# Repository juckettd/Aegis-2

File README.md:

# Aegis-2
The Aegis 2 Handheld with a 7" screen

NOTE: This is still a work in progress.

## Summary

The Aegis 2 is a DIY handheld that uses a 3D printed case with a Raspberry Pi CM4 and 1920x1200 7" screen.

## Building the Handheld

To build the handheld you will need the items listed as required in the Bill of Materials along with the following tools:

Reflow Station or Reflow Oven<br/>
Solding Iron<br/>
Solder Paste<br/>
Tweezers<br/>
Small Philips Screw Driver<br/>
Small Flathead Screw Driver<br/>
Super Glue (preferrably CA glue with Accelerator)

There are items in the Bill of Materials that are listed as optional. These items are not required to get a working device but can be used if desired. At this time I will not provide directions on how to use the optional components so use at your discretion.

### Assembling the Circuit Board

The custom circuit boards are provided as fusion 360 files in this repository. This includes the schematic, board layout, and the gerber files. 

To get the boards printed, a manufacturing facility is required. The website jlcpcb.com was used to print the 3 circuit board prototypes for the design. The larger of the two boards uses 4 layers, and the smaller ones use only 2 layers. It is recommended to also get the stencils with the boards so that applying the solder paste becomes much easier.

Once the boards have been received you will need to assemble the circuitry on the boards. This is done by getting all of the components provided in the bill of materials. Each item has a provided Link to where the item can be acquired along with the price at the time of the assembly of the prototype. After acquiring all of the components, use the stencil to apply solder paste to the circuit boards and then use tweezers to place each component. A reflow oven or reflow station should then be used to melt the solder paste and adhere the components. Lastly, any through hole components were then added on the using a soldering iron. 

Note: The teensy that is soldered to the board using the through holes. However, there are 4 pads that are located near the USB connector of the Teensy on the custom circuit board. They are the VBUS, D+, D-, and GND connections. I included the VBUS and GND connections as backups but they are not needed as the power and ground comes from the pins. But the D+, D- connections need to be connected to the teensy. On the underside of the teensy there are 4 pads that are in about the same location, a wire or some other form of connection is needed to connect the D+ from the teensy to the D+ on the custom circuit board, do the same with the D- connection.

While anyone who has experience with circuit boards will have their own method for assembling these boards I used the following steps and it is what I recommend for anyone without experience and a reflow oven (but a reflow station is required):
1. Using the stencil, put solder paste on the larger of the two boards on the side with a majority of the components
2. Place all of the surface mount components on that side of the board
3. Use a reflow station and heat the underside of the board until the solder paste on the top side melts to adhere the components. A tool to prop up the PCB comes in handy here. In my opinion this part is essential as some of the components are plastic and the hot air coming out of a reflow station can melt them.
4. Use a soldering iron to clean up an connections that didn't connect completely (You can watch youtube videos on how to do this, just search for solding iron and surface mount components)
5. Flip the board over and redo steps 1-4 for the underside of the board. Since these components are larger I just used the a soldering iron for all of the components, but the same procedure with the reflow station can be used. Just be careful with the hot air hitting components you have already put down, as they can fall off if the solder paste melts again.
6. Perform 1-5 for the second board and the few surface mount components that are on that board
7. Add all of the through hole items to both boards with a soldering iron (again youtube is your friend)

### Install Teensy Code

Before (or after) the circuit board has been assembled the teensy code needs to be pushed to the teensy. The teensy code is provided in the repo and you will need to follow the instructions on the teensy website for pushing code. Make sure that you set the board type to "XInput" otherwise it won't be seen as a XBox 360 Controller.

### 3D Printed Case

The files provided here for the case. They are printed in sections so that a printer with a standard bed size of 220mm x 220mm can be used print the case. Once they are printed they will have to be cleaned up and then glued together. Depending on which angle you choose to print the parts the cleanup step could be more or less cumbersome for the remove of support and getting good glue joints. I choose to print everything with flat surfaces on the bed to keep the post processing steps as easy as possible.

Once everything is glued together then no post processing on the outside is technically required to assemble the device. However, I chose to use filler, sand paper, and paint to get a really clean looking finish. The level of detail you desire on your handheld will be up to you based on how much effort you want to devote. Refer to youtube for how to sand and paint a 3D printed piece. However, try to keep the inside of the device as paint free as possible as the internal structure is already at the correct dimensions for the internal components.

I would also sand down the holes where the buttons will be located as they will to be rough from the 3D printing process. This can cause the buttons to stick. I would also check the shoulder buttons to make sure there is not any friction preventing them from moving properly. If there is then sand down the appropriate areas.

### Assembly

Once the case and the PCB have been built and are ready to go the handheld can be assembled.

TODO: Assembly Instructions

## Software

The Raspberry PI OS Buster version or Retropie both work. To get Bullseye working we need a new video driver that is not available yet. I've made a temporary one and will provide it here when I test it out.

The Config files provided that setup the device will install a monitor program that looks for the button presses for the power/reset/volume/misc. And like the previous handheld I built it will also eventually provide an overlay that will show battery/wifi status along with volume/brightness. However, the overlay does not work yet so that part of the code is commented out. But the monitor script does work for the buttons.

### /boot/config.txt

Regardless of which CM4 you use and which method is used to load the OS, you will need to add the following lines to the /boot/config.txt file. These are also listed in the /Config/boot/config.txt file in this repository:

dtoverlay=dwc2,dr_mode=host<br/>
h264_freq=333

The lines above will optimize the graphics for Moonlight (if you choose to use it to stream PC games) and will enable USB 2.0 on the device to get the Teensy and external USB ports working.

### First Boot

TODO

### System Setup

TODO

## Pictures/Videos

The are Videos of it working and Images are included in the Images folder:

Zelda: https://www.youtube.com/watch?v=uxBjKsduhgc

Super Mario World: https://www.youtube.com/watch?v=D417fbmwBnU

## Credits

Safe shutdown script
https://github.com/crcerror/ES-generic-shutdown/blob/master/multi_switch.sh

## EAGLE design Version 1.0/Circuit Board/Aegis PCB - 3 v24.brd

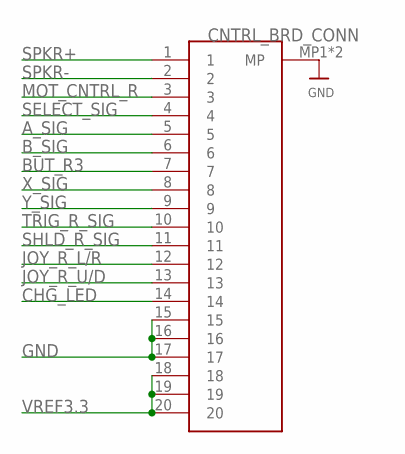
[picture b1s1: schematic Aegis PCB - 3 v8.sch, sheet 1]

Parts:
CNTRL_BRD_CONN: CONN-0527462033

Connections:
A_SIG: CNTRL_BRD_CONN.5; also elsewhere on the board
BUT_R3: CNTRL_BRD_CONN.7; also elsewhere on the board
B_SIG: CNTRL_BRD_CONN.6; also elsewhere on the board
CHG_LED: CNTRL_BRD_CONN.14; also elsewhere on the board
GND: CNTRL_BRD_CONN.15, CNTRL_BRD_CONN.16, CNTRL_BRD_CONN.17, CNTRL_BRD_CONN.MP1 (MP), CNTRL_BRD_CONN.MP2 (MP); also elsewhere on the board
JOY_R_L/R: CNTRL_BRD_CONN.12; also elsewhere on the board
JOY_R_U/D: CNTRL_BRD_CONN.13; also elsewhere on the board
MOT_CNTRL_R: CNTRL_BRD_CONN.3; also elsewhere on the board
SELECT_SIG: CNTRL_BRD_CONN.4; also elsewhere on the board
SHLD_R_SIG: CNTRL_BRD_CONN.11; also elsewhere on the board
SPKR+: CNTRL_BRD_CONN.1; also elsewhere on the board
SPKR-: CNTRL_BRD_CONN.2; also elsewhere on the board
TRIG_R_SIG: CNTRL_BRD_CONN.10; also elsewhere on the board
VREF3.3: CNTRL_BRD_CONN.18, CNTRL_BRD_CONN.19, CNTRL_BRD_CONN.20; also elsewhere on the board
X_SIG: CNTRL_BRD_CONN.8; also elsewhere on the board
Y_SIG: CNTRL_BRD_CONN.9; also elsewhere on the board

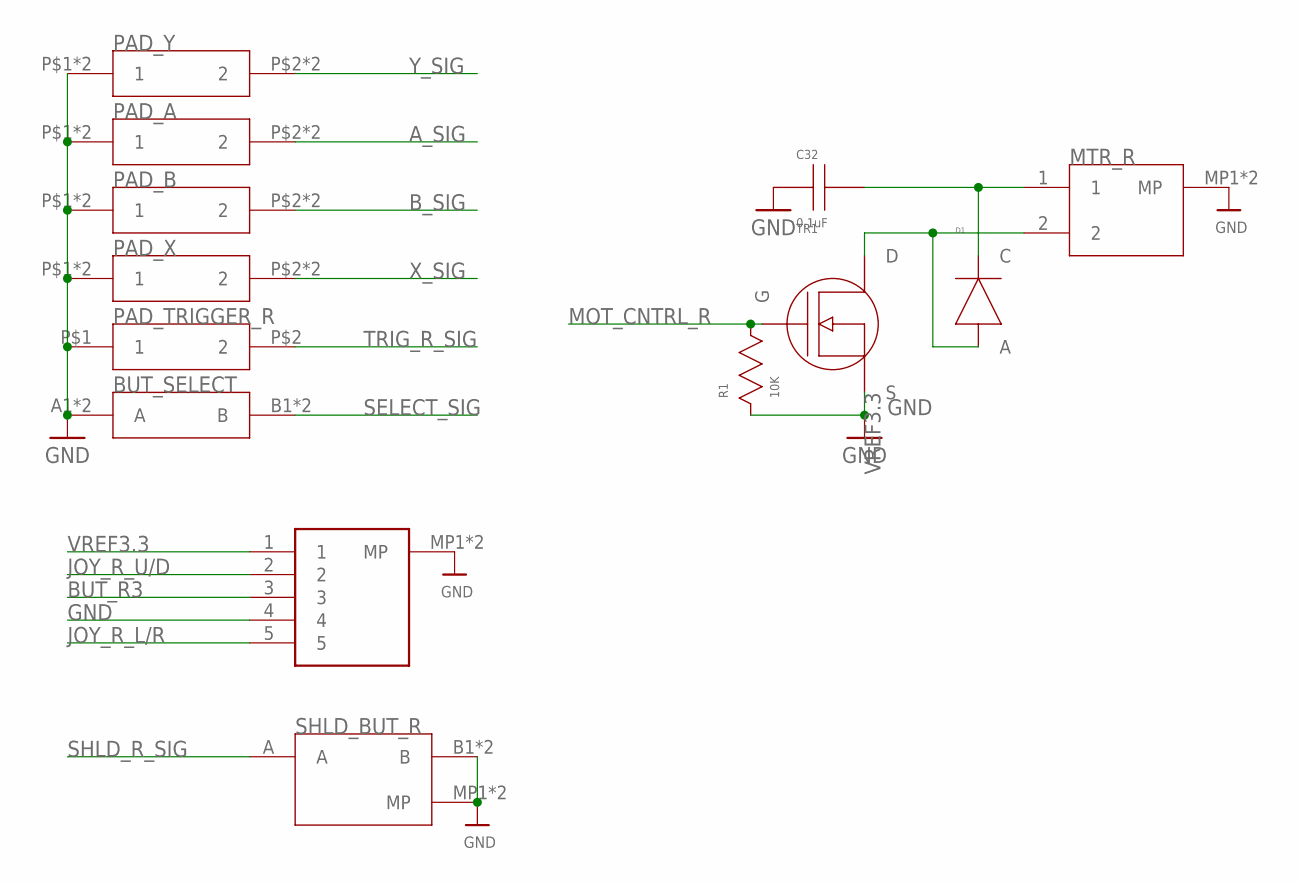
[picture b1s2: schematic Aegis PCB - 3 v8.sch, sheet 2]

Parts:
BUT_SELECT: BUT-R-667834
C32: 0.1uF; CAP-603
D1: DIODE-X3-WLB1608-2
JOYSTICK_R: CONN-046809605110846+
MTR_R: CONN-0781710002
PAD_A: AEGIS-BUTTONPAD
PAD_B: AEGIS-BUTTONPAD
PAD_TRIGGER_R: AEGIN-SHLDPAD
PAD_X: AEGIS-BUTTONPAD
PAD_Y: AEGIS-BUTTONPAD
R1: 10K; RES-603
SHLD_BUT_R: AEGIN-SHLDBUT
TR1: TRAN-DMG2302UKQ

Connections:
A_SIG: PAD_A.P$2 (2), PAD_A.P$4 (2); also elsewhere on the board
BUT_R3: JOYSTICK_R.3; also elsewhere on the board
B_SIG: PAD_B.P$2 (2), PAD_B.P$4 (2); also elsewhere on the board
GND: BUT_SELECT.A1 (A), BUT_SELECT.A2 (A), C32.A, JOYSTICK_R.4, JOYSTICK_R.MP1 (MP), JOYSTICK_R.MP2 (MP), MTR_R.MP1 (MP), MTR_R.MP2 (MP), PAD_A.P$1 (1), PAD_A.P$3 (1), PAD_B.P$1 (1), PAD_B.P$3 (1), PAD_TRIGGER_R.P$1 (1), PAD_X.P$1 (1), PAD_X.P$3 (1), PAD_Y.P$1 (1), PAD_Y.P$3 (1), R1.A, SHLD_BUT_R.B1 (B), SHLD_BUT_R.B2 (B), SHLD_BUT_R.MP1 (MP), SHLD_BUT_R.MP2 (MP), TR1.S; also elsewhere on the board
JOY_R_L/R: JOYSTICK_R.5; also elsewhere on the board
JOY_R_U/D: JOYSTICK_R.2; also elsewhere on the board
MOT_CNTRL_R: R1.C, TR1.G; also elsewhere on the board
unnamed: D1.A, MTR_R.2, TR1.D
SELECT_SIG: BUT_SELECT.B1 (B), BUT_SELECT.B2 (B); also elsewhere on the board
SHLD_R_SIG: SHLD_BUT_R.A; also elsewhere on the board
TRIG_R_SIG: PAD_TRIGGER_R.P$2 (2); also elsewhere on the board
VREF3.3: C32.C, D1.C, JOYSTICK_R.1, MTR_R.1; also elsewhere on the board
X_SIG: PAD_X.P$2 (2), PAD_X.P$4 (2); also elsewhere on the board
Y_SIG: PAD_Y.P$2 (2), PAD_Y.P$4 (2); also elsewhere on the board

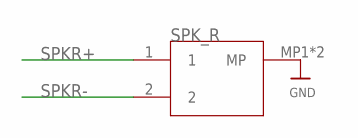
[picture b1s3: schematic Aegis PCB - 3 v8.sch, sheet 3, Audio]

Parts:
SPK_R: CONN-0781710002

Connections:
GND: SPK_R.MP1 (MP), SPK_R.MP2 (MP); also elsewhere on the board
SPKR+: SPK_R.1; also elsewhere on the board
SPKR-: SPK_R.2; also elsewhere on the board

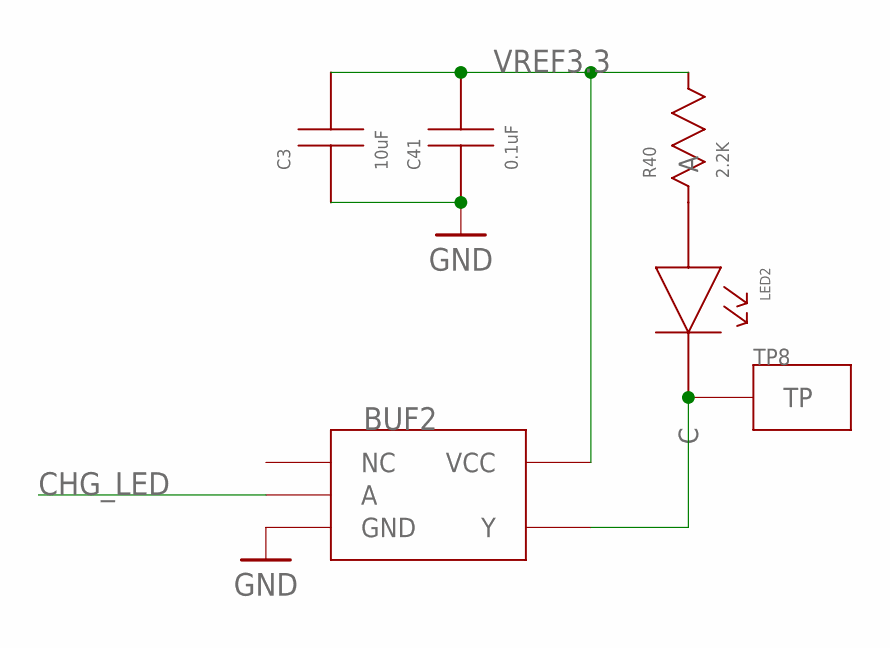
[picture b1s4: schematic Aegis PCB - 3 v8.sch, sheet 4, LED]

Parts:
BUF2: BUF-74LVC1G07
C3: 10uF; CAP-603
C41: 0.1uF; CAP-603
LED2: LED-SM0805UWC
R40: 2.2K; RES-603
TP8: TESTPOINT

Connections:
CHG_LED: BUF2.A; also elsewhere on the board
GND: BUF2.GND, C3.A, C41.A; also elsewhere on the board
unnamed: LED2.A, R40.A
unnamed: BUF2.Y, LED2.C, TP8.TP
VREF3.3: BUF2.VCC, C3.C, C41.C, R40.C; also elsewhere on the board

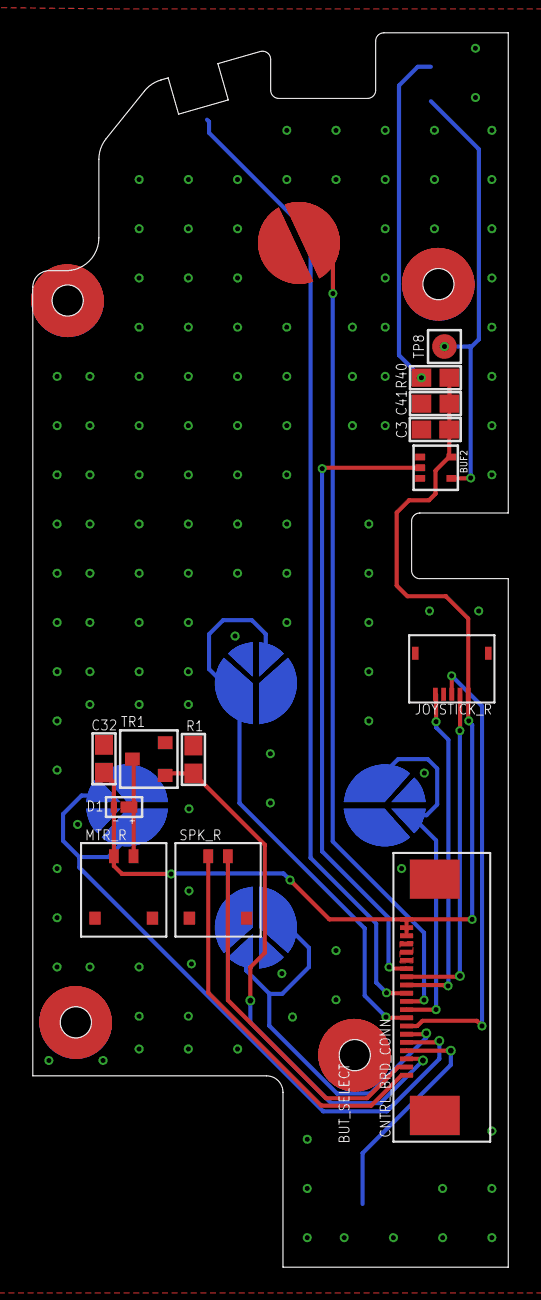
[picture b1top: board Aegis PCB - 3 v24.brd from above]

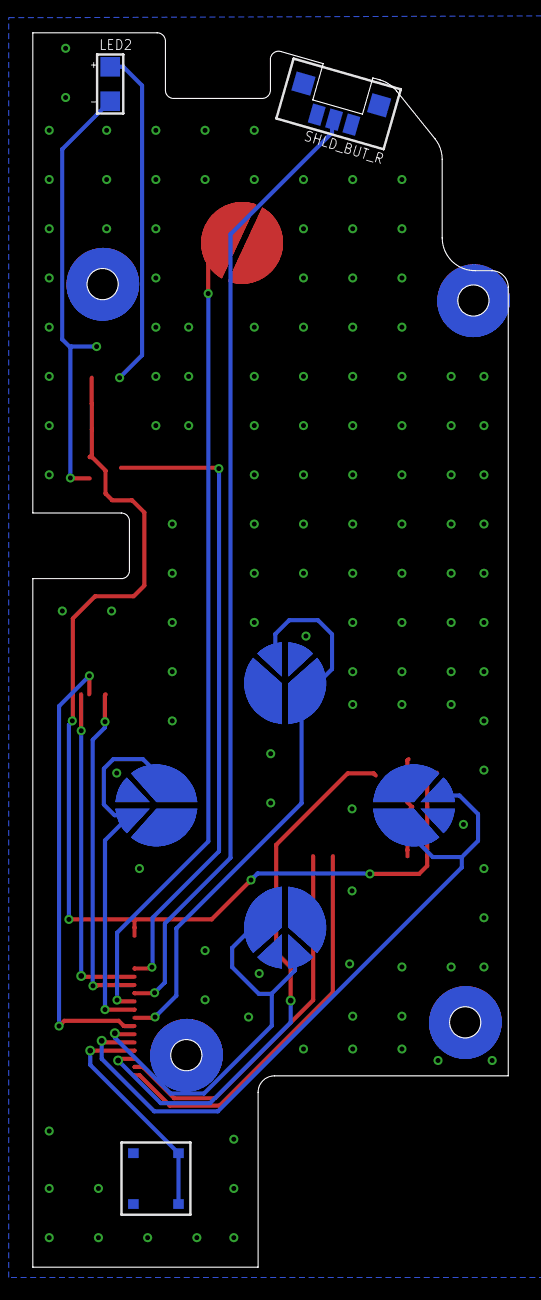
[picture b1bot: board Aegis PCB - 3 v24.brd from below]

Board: 2 copper layers, 29.0 x 75.2 mm, 21 parts (7 on the bottom side), 19 nets.

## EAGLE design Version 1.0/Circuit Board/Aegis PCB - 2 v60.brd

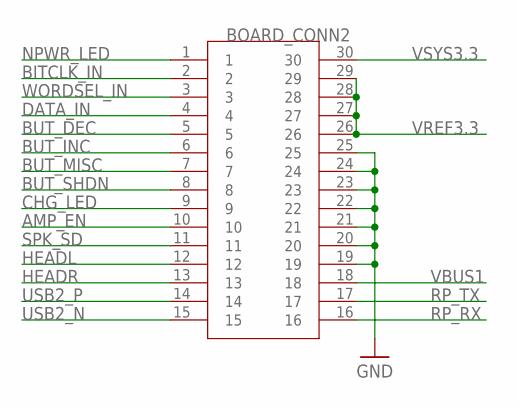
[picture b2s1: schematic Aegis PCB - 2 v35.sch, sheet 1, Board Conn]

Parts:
BOARD_CONN2: CONN-AXK6F30347YG

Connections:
AMP_EN: BOARD_CONN2.10; also elsewhere on the board
BITCLK_IN: BOARD_CONN2.2; also elsewhere on the board
BUT_DEC: BOARD_CONN2.5; also elsewhere on the board
BUT_INC: BOARD_CONN2.6; also elsewhere on the board
BUT_MISC: BOARD_CONN2.7; also elsewhere on the board
BUT_SHDN: BOARD_CONN2.8; also elsewhere on the board
CHG_LED: BOARD_CONN2.9; also elsewhere on the board
DATA_IN: BOARD_CONN2.4; also elsewhere on the board
GND: BOARD_CONN2.19, BOARD_CONN2.20, BOARD_CONN2.21, BOARD_CONN2.22, BOARD_CONN2.23, BOARD_CONN2.24, BOARD_CONN2.25; also elsewhere on the board
HEADL: BOARD_CONN2.12; also elsewhere on the board
HEADR: BOARD_CONN2.13; also elsewhere on the board
NPWR_LED: BOARD_CONN2.1; also elsewhere on the board
RP_RX: BOARD_CONN2.16; also elsewhere on the board
RP_TX: BOARD_CONN2.17; also elsewhere on the board
SPK_SD: BOARD_CONN2.11; also elsewhere on the board
USB2_N: BOARD_CONN2.15; also elsewhere on the board
USB2_P: BOARD_CONN2.14; also elsewhere on the board
VBUS1: BOARD_CONN2.18; also elsewhere on the board
VREF3.3: BOARD_CONN2.26, BOARD_CONN2.27, BOARD_CONN2.28, BOARD_CONN2.29; also elsewhere on the board
VSYS3.3: BOARD_CONN2.30; also elsewhere on the board
WORDSEL_IN: BOARD_CONN2.3; also elsewhere on the board

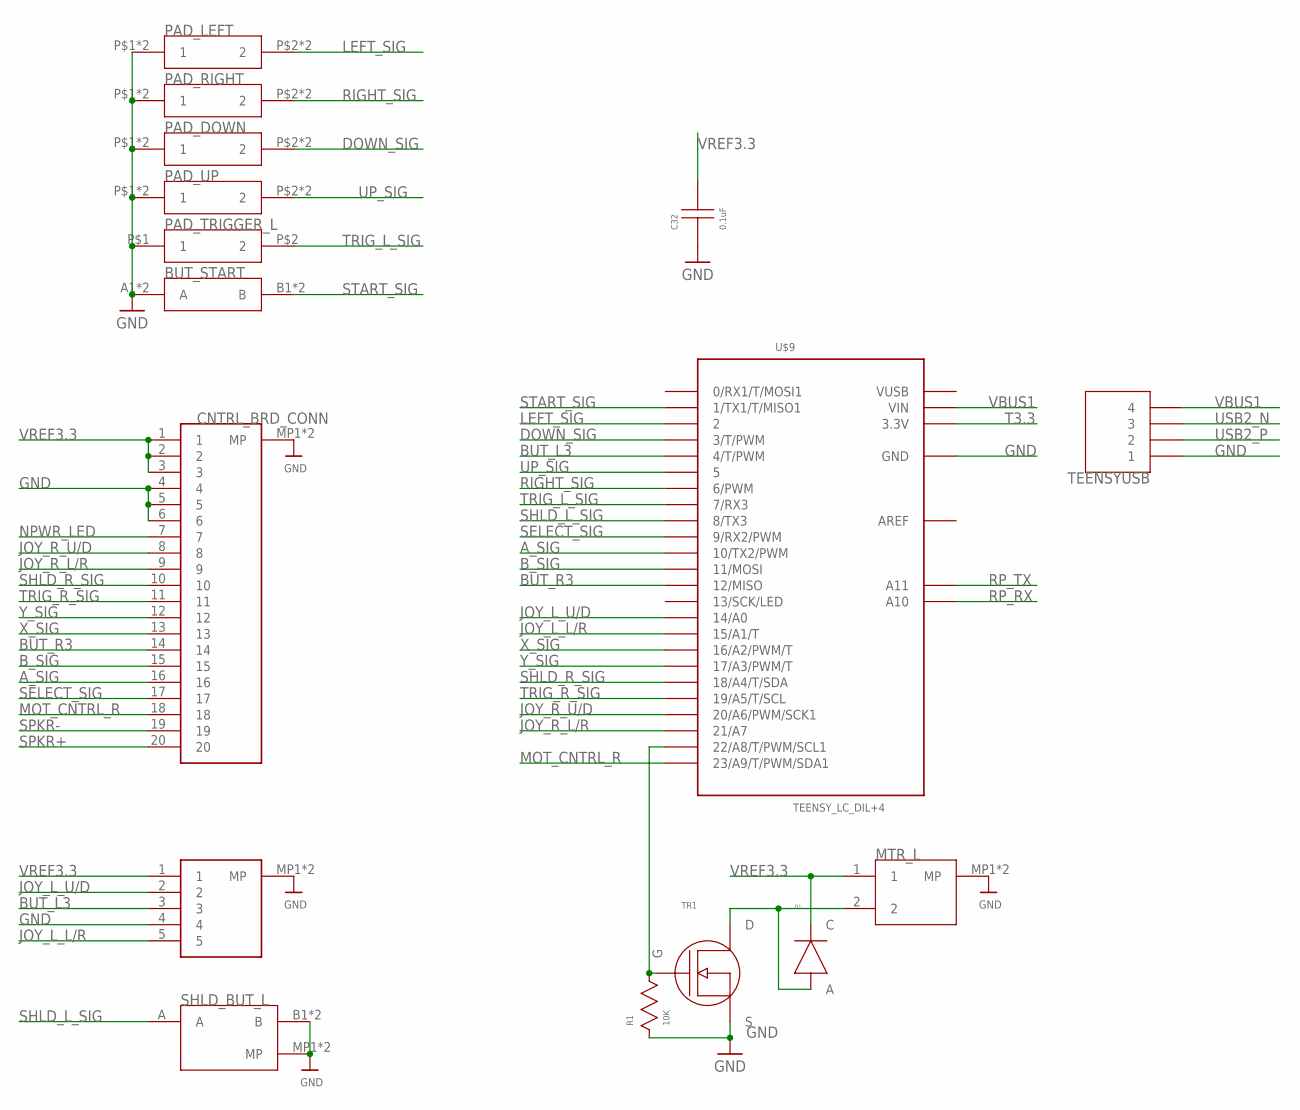
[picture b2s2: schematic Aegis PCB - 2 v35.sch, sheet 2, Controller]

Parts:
BUT_START: BUT-R-667834
C32: 0.1uF; CAP-603
CNTRL_BRD_CONN: CONN-0527462033
D1: DIODE-X3-WLB1608-2
JOYSTICK_L: CONN-046809605110846+
MTR_L: CONN-0781710002
PAD_DOWN: AEGIS-BUTTONPAD
PAD_LEFT: AEGIS-BUTTONPAD
PAD_RIGHT: AEGIS-BUTTONPAD
PAD_TRIGGER_L: AEGIN-SHLDPAD
PAD_UP: AEGIS-BUTTONPAD
R1: 10K; RES-603
SHLD_BUT_L: AEGIN-SHLDBUT
TEENSYUSB: CONN_4PIN
TR1: TRAN-DMG2302UKQ
U$9: TEENSY_LC_DIL+4; TEENSY_3.0-3.2&LC_DIL+4

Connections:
AREF: U$9.AREF
A_SIG: CNTRL_BRD_CONN.16, U$9.10 (10/TX2/PWM)
BUT_L3: JOYSTICK_L.3, U$9.4 (4/T/PWM)
BUT_R3: CNTRL_BRD_CONN.14, U$9.12 (12/MISO)
B_SIG: CNTRL_BRD_CONN.15, U$9.11 (11/MOSI)
DOWN_SIG: PAD_DOWN.P$2 (2), PAD_DOWN.P$4 (2), U$9.3 (3/T/PWM)
GND: BUT_START.A1 (A), BUT_START.A2 (A), C32.A, CNTRL_BRD_CONN.4, CNTRL_BRD_CONN.5, CNTRL_BRD_CONN.6, CNTRL_BRD_CONN.MP1 (MP), CNTRL_BRD_CONN.MP2 (MP), JOYSTICK_L.4, JOYSTICK_L.MP1 (MP), JOYSTICK_L.MP2 (MP), MTR_L.MP1 (MP), MTR_L.MP2 (MP), PAD_DOWN.P$1 (1), PAD_DOWN.P$3 (1), PAD_LEFT.P$1 (1), PAD_LEFT.P$3 (1), PAD_RIGHT.P$1 (1), PAD_RIGHT.P$3 (1), PAD_TRIGGER_L.P$1 (1), PAD_UP.P$1 (1), PAD_UP.P$3 (1), R1.A, SHLD_BUT_L.B1 (B), SHLD_BUT_L.B2 (B), SHLD_BUT_L.MP1 (MP), SHLD_BUT_L.MP2 (MP), TEENSYUSB.1, TR1.S, U$9.AGND (GND), U$9.GND; also elsewhere on the board
JOY_L_L/R: JOYSTICK_L.5, U$9.15/A1 (15/A1/T)
JOY_L_U/D: JOYSTICK_L.2, U$9.14/A0
JOY_R_L/R: CNTRL_BRD_CONN.9, U$9.21/A7
JOY_R_U/D: CNTRL_BRD_CONN.8, U$9.20/A6 (20/A6/PWM/SCK1)
LEFT_SIG: PAD_LEFT.P$2 (2), PAD_LEFT.P$4 (2), U$9.2
MOT_CNTRL_R: CNTRL_BRD_CONN.18, U$9.23/A9 (23/A9/T/PWM/SDA1)
unnamed: R1.C, TR1.G, U$9.22/A8 (22/A8/T/PWM/SCL1)
unnamed: D1.A, MTR_L.2, TR1.D
NPWR_LED: CNTRL_BRD_CONN.7; also elsewhere on the board
RIGHT_SIG: PAD_RIGHT.P$2 (2), PAD_RIGHT.P$4 (2), U$9.6 (6/PWM)
RP_RX: U$9.A10; also elsewhere on the board
RP_TX: U$9.A11; also elsewhere on the board
SELECT_SIG: CNTRL_BRD_CONN.17, U$9.9 (9/RX2/PWM)
SHLD_L_SIG: SHLD_BUT_L.A, U$9.8 (8/TX3)
SHLD_R_SIG: CNTRL_BRD_CONN.10, U$9.18/A4 (18/A4/T/SDA)
SPKR+: CNTRL_BRD_CONN.20; also elsewhere on the board
SPKR-: CNTRL_BRD_CONN.19; also elsewhere on the board
START_SIG: BUT_START.B1 (B), BUT_START.B2 (B), U$9.1 (1/TX1/T/MISO1)
T3.3: U$9.3.3V
TRIG_L_SIG: PAD_TRIGGER_L.P$2 (2), U$9.7 (7/RX3)
TRIG_R_SIG: CNTRL_BRD_CONN.11, U$9.19/A5 (19/A5/T/SCL)
UP_SIG: PAD_UP.P$2 (2), PAD_UP.P$4 (2), U$9.5
USB2_N: TEENSYUSB.3; also elsewhere on the board
USB2_P: TEENSYUSB.2; also elsewhere on the board
VBUS1: TEENSYUSB.4, U$9.VIN; also elsewhere on the board
VREF3.3: C32.C, CNTRL_BRD_CONN.1, CNTRL_BRD_CONN.2, CNTRL_BRD_CONN.3, D1.C, JOYSTICK_L.1, MTR_L.1; also elsewhere on the board
VUSB: U$9.VUSB
X_SIG: CNTRL_BRD_CONN.13, U$9.16/A2 (16/A2/PWM/T)
Y_SIG: CNTRL_BRD_CONN.12, U$9.17/A3 (17/A3/PWM/T)

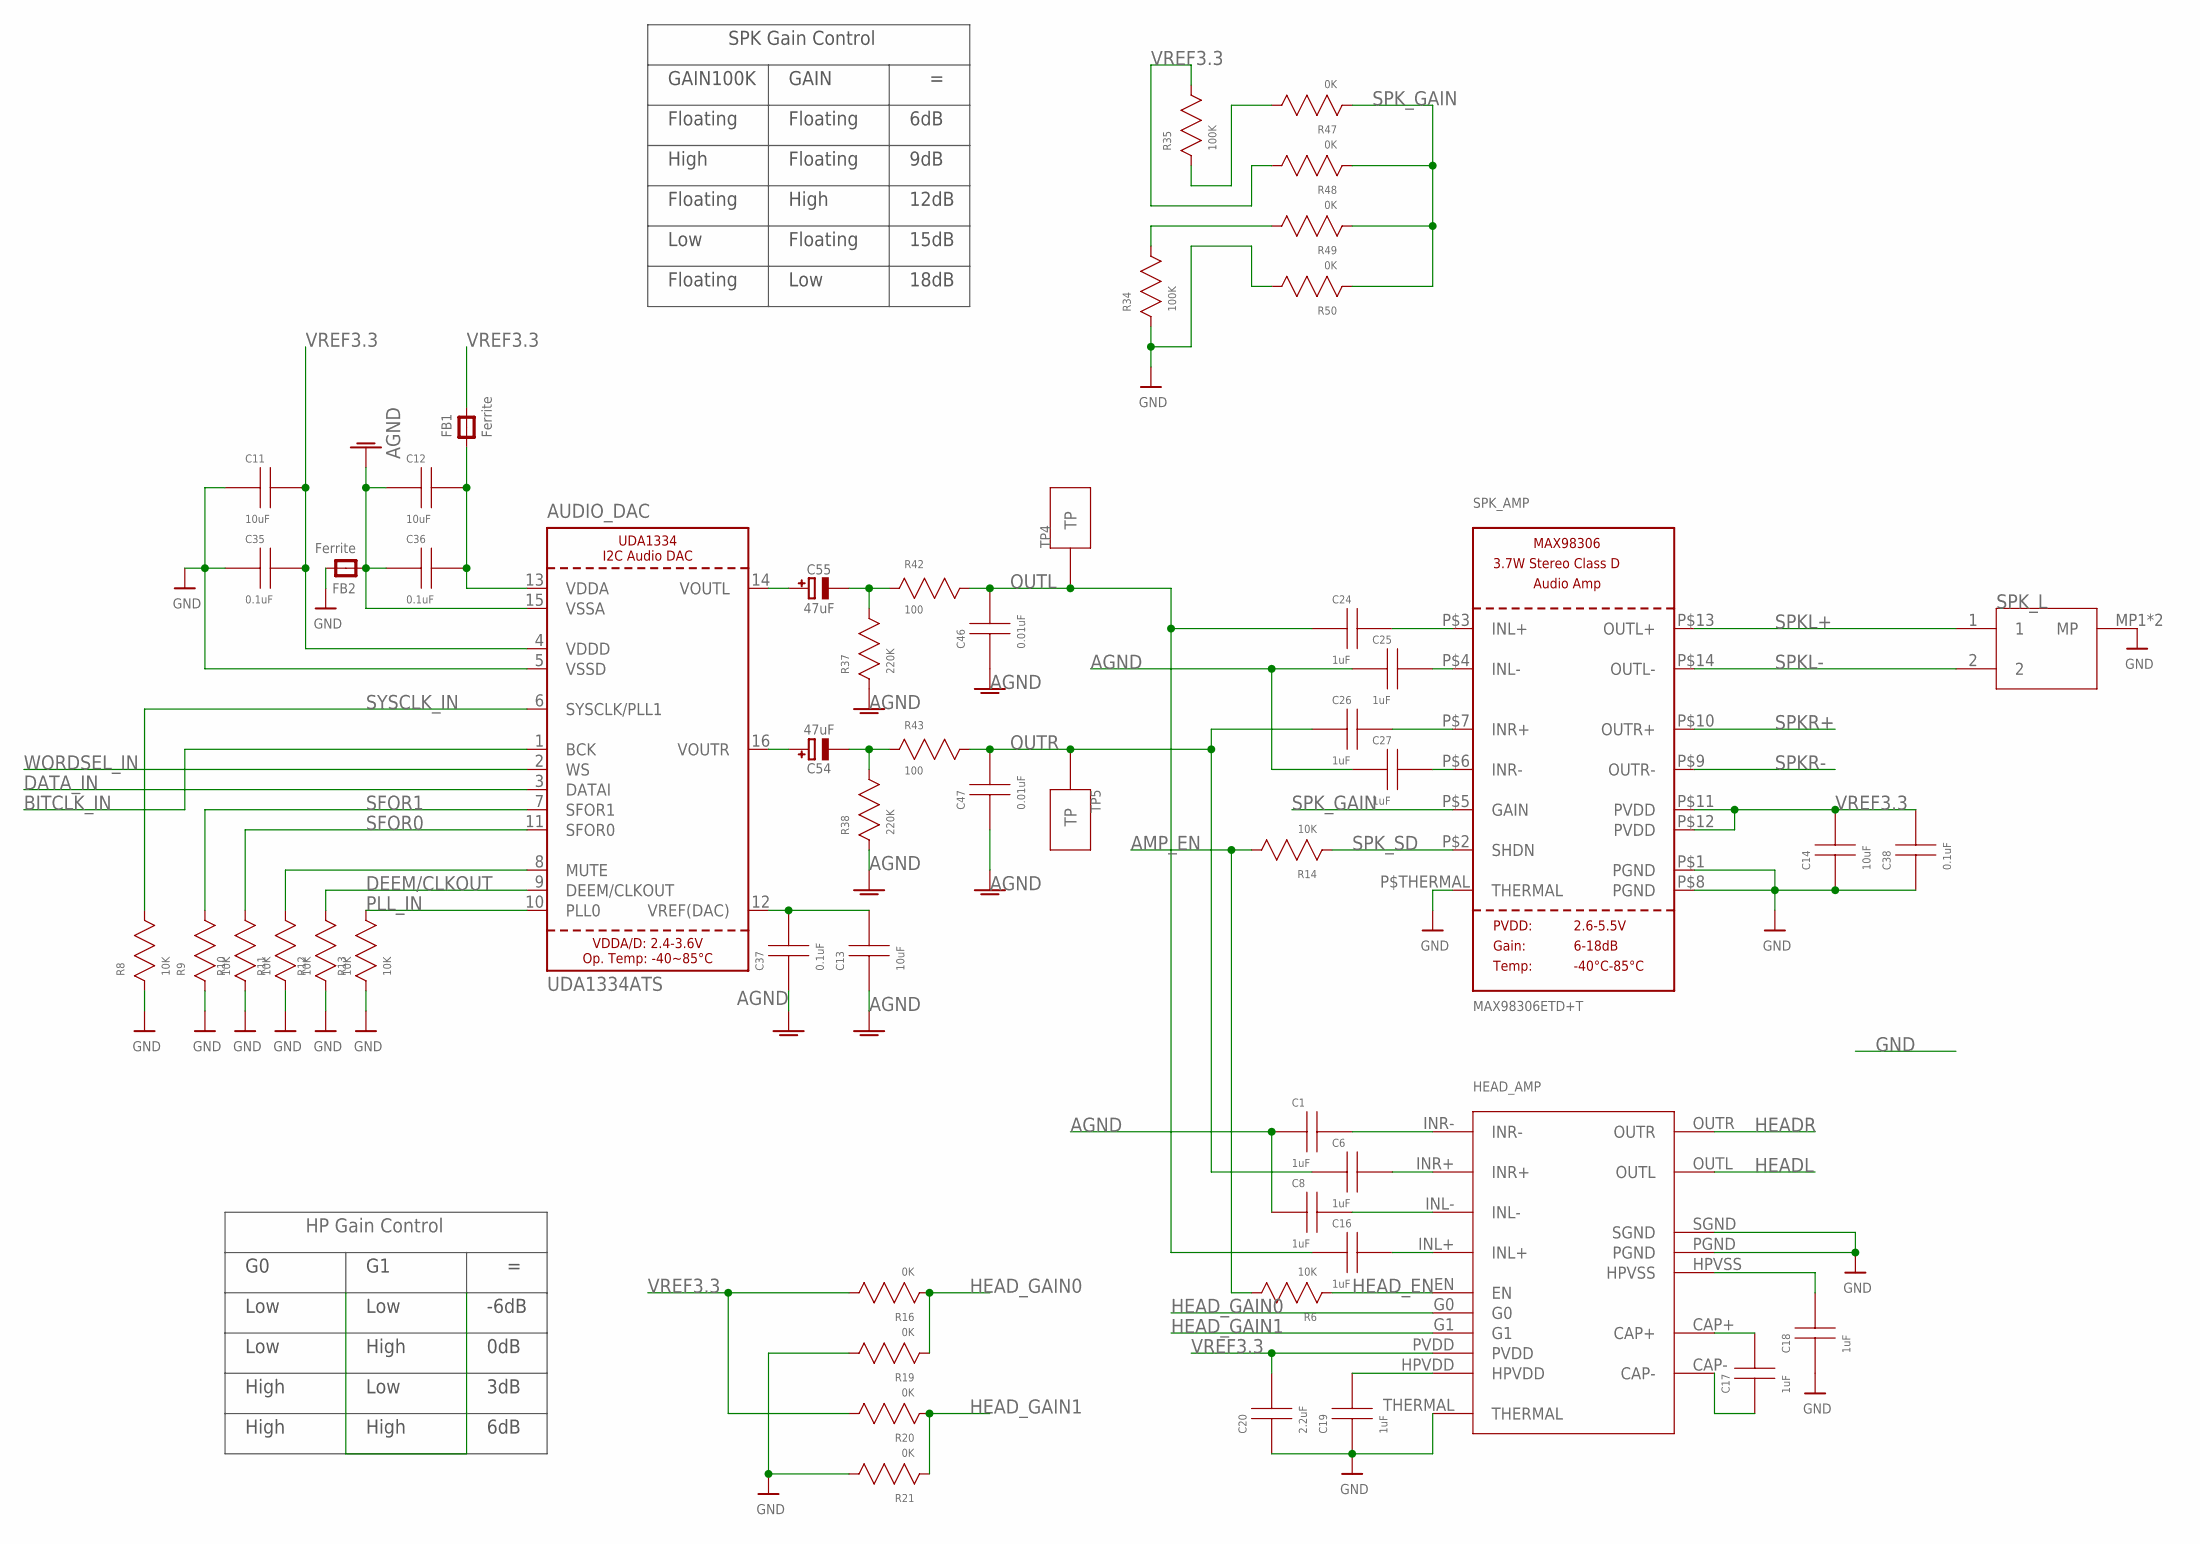
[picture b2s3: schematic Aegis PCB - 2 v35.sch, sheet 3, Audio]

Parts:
AUDIO_DAC: UDA1334ATS; SSOP16_4.4MM
C1, C6, C8, C16, C17, C18, C19, C24, C25, C26, C27: 1uF; CAP-603
C11, C12, C13, C14: 10uF; CAP-603
C20: 2.2uF; CAP-603
C35, C36, C37, C38: 0.1uF; CAP-603
C46, C47: 0.01uF; CAP-603
C54, C55: 47uF; PANASONIC_C
FB1, FB2: Ferrite; 0805@1
HEAD_AMP: IC-PAM8908
R6, R8, R9, R10, R11, R12, R13, R14: 10K; RES-603
R16, R19, R20, R21, R47, R48, R49, R50: 0K; RES-603
R34, R35: 100K; RES-603
R37, R38: 220K; RES-603
R42, R43: 100; RES-603
SPK_AMP: MAX98306ETD+T; TDFN14_3X3MM
SPK_L: CONN-0781710002
TP4, TP5: TESTPOINT

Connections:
AGND: AUDIO_DAC.15 (VSSA), C1.A, C8.A, C12.A, C13.A, C25.A, C27.A, C36.A, C37.A, C46.A, C47.A, FB2.1, R37.A, R38.A
AMP_EN: R6.C, R14.C; also elsewhere on the board
BITCLK_IN: AUDIO_DAC.1 (BCK); also elsewhere on the board
DATA_IN: AUDIO_DAC.3 (DATAI); also elsewhere on the board
DEEM/CLKOUT: AUDIO_DAC.9 (DEEM/CLKOUT), R12.C
GND: AUDIO_DAC.5 (VSSD), C11.A, C14.A, C18.A, C19.A, C20.A, C35.A, C38.A, FB2.2, HEAD_AMP.PGND, HEAD_AMP.SGND, HEAD_AMP.THERMAL, R8.A, R9.A, R10.A, R11.A, R12.A, R13.A, R19.C, R21.C, R34.A, R50.C, SPK_AMP.P$1 (PGND), SPK_AMP.P$8 (PGND), SPK_AMP.P$THERMAL (THERMAL), SPK_L.MP1 (MP), SPK_L.MP2 (MP); also elsewhere on the board
HEADL: HEAD_AMP.OUTL; also elsewhere on the board
HEADR: HEAD_AMP.OUTR; also elsewhere on the board
HEAD_EN: HEAD_AMP.EN, R6.A
HEAD_GAIN0: HEAD_AMP.G0, R16.A, R19.A
HEAD_GAIN1: HEAD_AMP.G1, R20.A, R21.A
unnamed: AUDIO_DAC.8 (MUTE), R11.C
unnamed: AUDIO_DAC.13 (VDDA), C12.C, C36.C, FB1.1
unnamed: C54.-, R38.C, R43.A
unnamed: C55.-, R37.C, R42.A
unnamed: C1.C, HEAD_AMP.INR-
unnamed: AUDIO_DAC.12 (VREF(DAC)), C13.C, C37.C
unnamed: AUDIO_DAC.16 (VOUTR), C54.+
unnamed: AUDIO_DAC.14 (VOUTL), C55.+
unnamed: R35.A, R47.C
unnamed: R34.C, R49.C
unnamed: C24.C, SPK_AMP.P$3 (INL+)
unnamed: C25.C, SPK_AMP.P$4 (INL-)
unnamed: C26.C, SPK_AMP.P$7 (INR+)
unnamed: C27.C, SPK_AMP.P$6 (INR-)
unnamed: C6.C, HEAD_AMP.INR+
unnamed: C16.C, HEAD_AMP.INL+
unnamed: C8.C, HEAD_AMP.INL-
unnamed: C17.C, HEAD_AMP.CAP+
unnamed: C17.A, HEAD_AMP.CAP-
unnamed: C18.C, HEAD_AMP.HPVSS
unnamed: C19.C, HEAD_AMP.HPVDD
OUTL: C16.A, C24.A, C46.C, R42.C, TP4.TP
OUTR: C6.A, C26.A, C47.C, R43.C, TP5.TP
PLL_IN: AUDIO_DAC.10 (PLL0), R13.C
SFOR0: AUDIO_DAC.11 (SFOR0), R10.C
SFOR1: AUDIO_DAC.7 (SFOR1), R9.C
SPKL+: SPK_AMP.P$13 (OUTL+), SPK_L.1
SPKL-: SPK_AMP.P$14 (OUTL-), SPK_L.2
SPKR+: SPK_AMP.P$10 (OUTR+); also elsewhere on the board
SPKR-: SPK_AMP.P$9 (OUTR-); also elsewhere on the board
SPK_GAIN: R47.A, R48.A, R49.A, R50.A, SPK_AMP.P$5 (GAIN)
SPK_SD: R14.A, SPK_AMP.P$2 (SHDN); also elsewhere on the board
SYSCLK_IN: AUDIO_DAC.6 (SYSCLK/PLL1), R8.C
VREF3.3: AUDIO_DAC.4 (VDDD), C11.C, C14.C, C20.C, C35.C, C38.C, FB1.2, HEAD_AMP.PVDD, R16.C, R20.C, R35.C, R48.C, SPK_AMP.P$11 (PVDD), SPK_AMP.P$12 (PVDD); also elsewhere on the board
WORDSEL_IN: AUDIO_DAC.2 (WS); also elsewhere on the board

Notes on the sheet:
GAIN100K
GAIN
Floating
6dB
High
9dB
12dB
Low
15dB
18dB
SPK Gain Control
-6dB
0dB
3dB
HP Gain Control

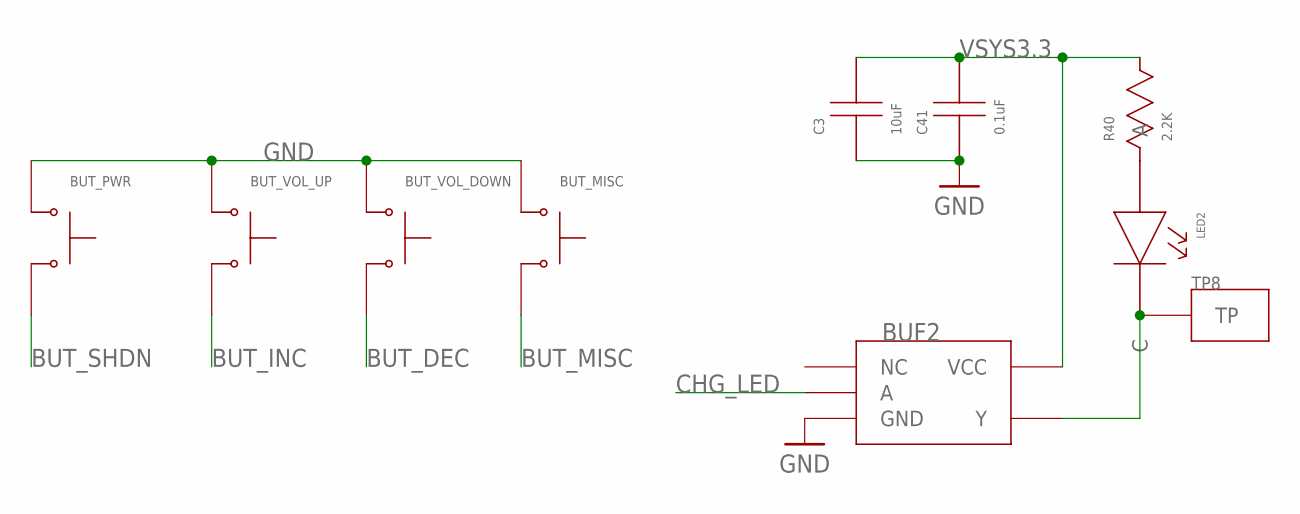
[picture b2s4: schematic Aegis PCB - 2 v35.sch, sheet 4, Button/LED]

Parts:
BUF2: BUF-74LVC1G07
BUT_MISC: BUT-KSS331GLFS
BUT_PWR: BUT-KSS331GLFS
BUT_VOL_DOWN: BUT-KSS331GLFS
BUT_VOL_UP: BUT-KSS331GLFS
C3: 10uF; CAP-603
C41: 0.1uF; CAP-603
LED2: LED-SM0805UWC
R40: 2.2K; RES-603
TP8: TESTPOINT

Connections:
BUT_DEC: BUT_VOL_DOWN.2; also elsewhere on the board
BUT_INC: BUT_VOL_UP.2; also elsewhere on the board
BUT_MISC: BUT_MISC.2; also elsewhere on the board
BUT_SHDN: BUT_PWR.2; also elsewhere on the board
CHG_LED: BUF2.A; also elsewhere on the board
GND: BUF2.GND, BUT_MISC.1, BUT_PWR.1, BUT_VOL_DOWN.1, BUT_VOL_UP.1, C3.A, C41.A; also elsewhere on the board
unnamed: LED2.A, R40.A
unnamed: BUF2.Y, LED2.C, TP8.TP
VSYS3.3: BUF2.VCC, C3.C, C41.C, R40.C; also elsewhere on the board

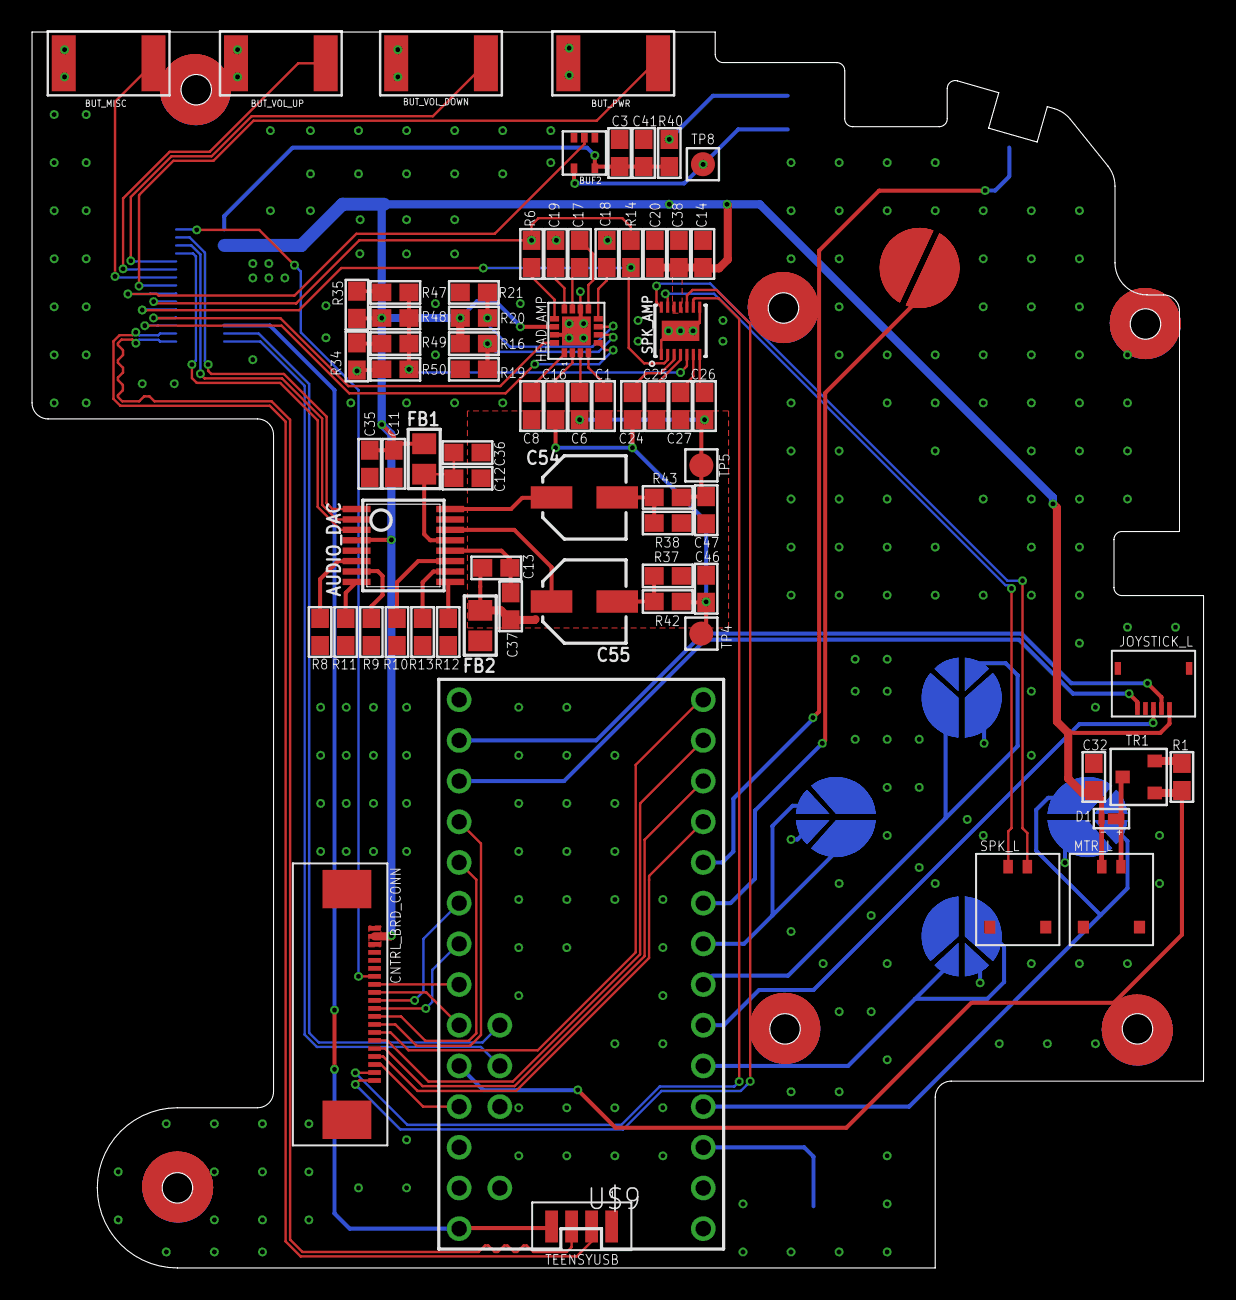
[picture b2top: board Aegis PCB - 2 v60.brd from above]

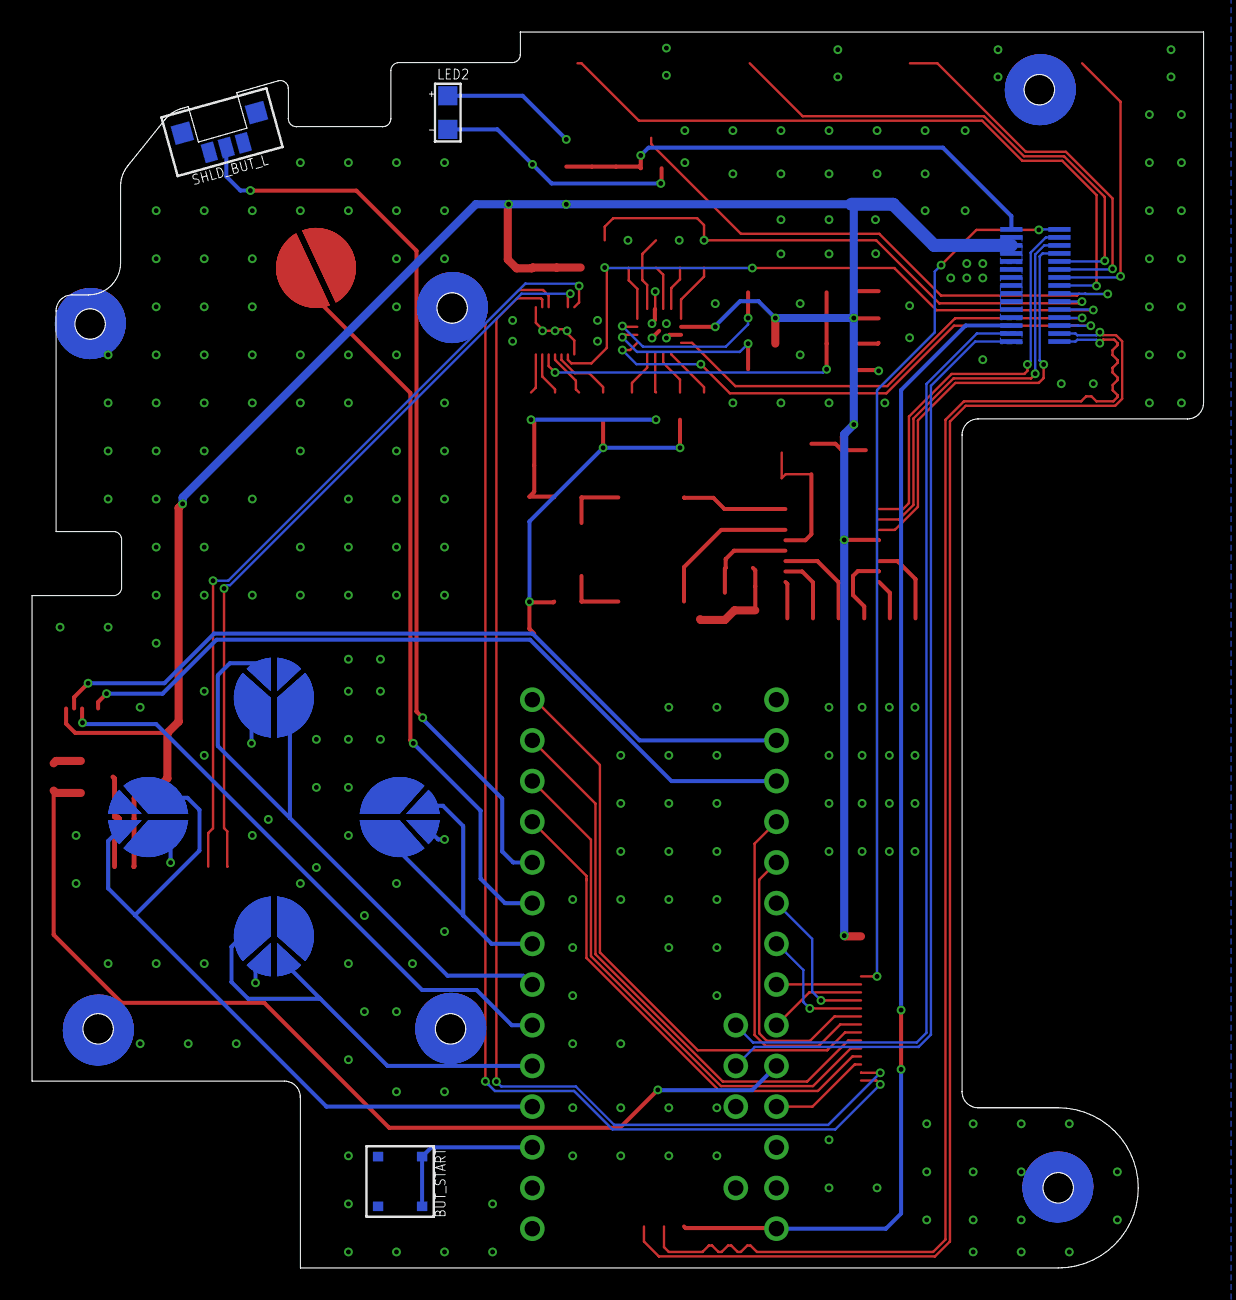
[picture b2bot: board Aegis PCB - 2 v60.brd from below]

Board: 2 copper layers, 73.1 x 77.2 mm, 81 parts (8 on the bottom side), 83 nets.

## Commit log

2022-07-19 Create LICENSE
2022-07-19 Adding initial files. Still WIP
2022-07-28 Adding updated circuit boards and gerber files
2023-05-09 Updated the CAD files and provided a BOM
2023-05-09 Updated the battery on the BOM to the correct one
2023-05-09 Adding the Panel Driver for the screen for Bullseye Updating the monitor.c file so that the buttons work with the KMS driver even though the display still does not Added the WiringPi folder in case t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
2023-05-09 Update README.md
    fixing spelling errors in README
2023-05-09 Update README.md
    Updating README for the config files
2023-05-10 Adding internal supports for the back center case piece
2025-10-16 feat: adding new files I never got around to adding.
2025-10-16 feat: adding images and alternate circuit board
2025-10-16 Update README with video links
    Added links to videos demonstrating functionality.
2025-12-13 feat: added updated BOM, new controller code for better button debouncing and a version of the controller code that supports calibration for the joysticks.
2025-12-13 feat: added the clear acrylic sheet to the BOM for the front of the screen

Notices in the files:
parts and their libraries:
microbuilder: This work is placed in the public domain, and may be freely used for commercial and non-commercial work with the following conditions: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
